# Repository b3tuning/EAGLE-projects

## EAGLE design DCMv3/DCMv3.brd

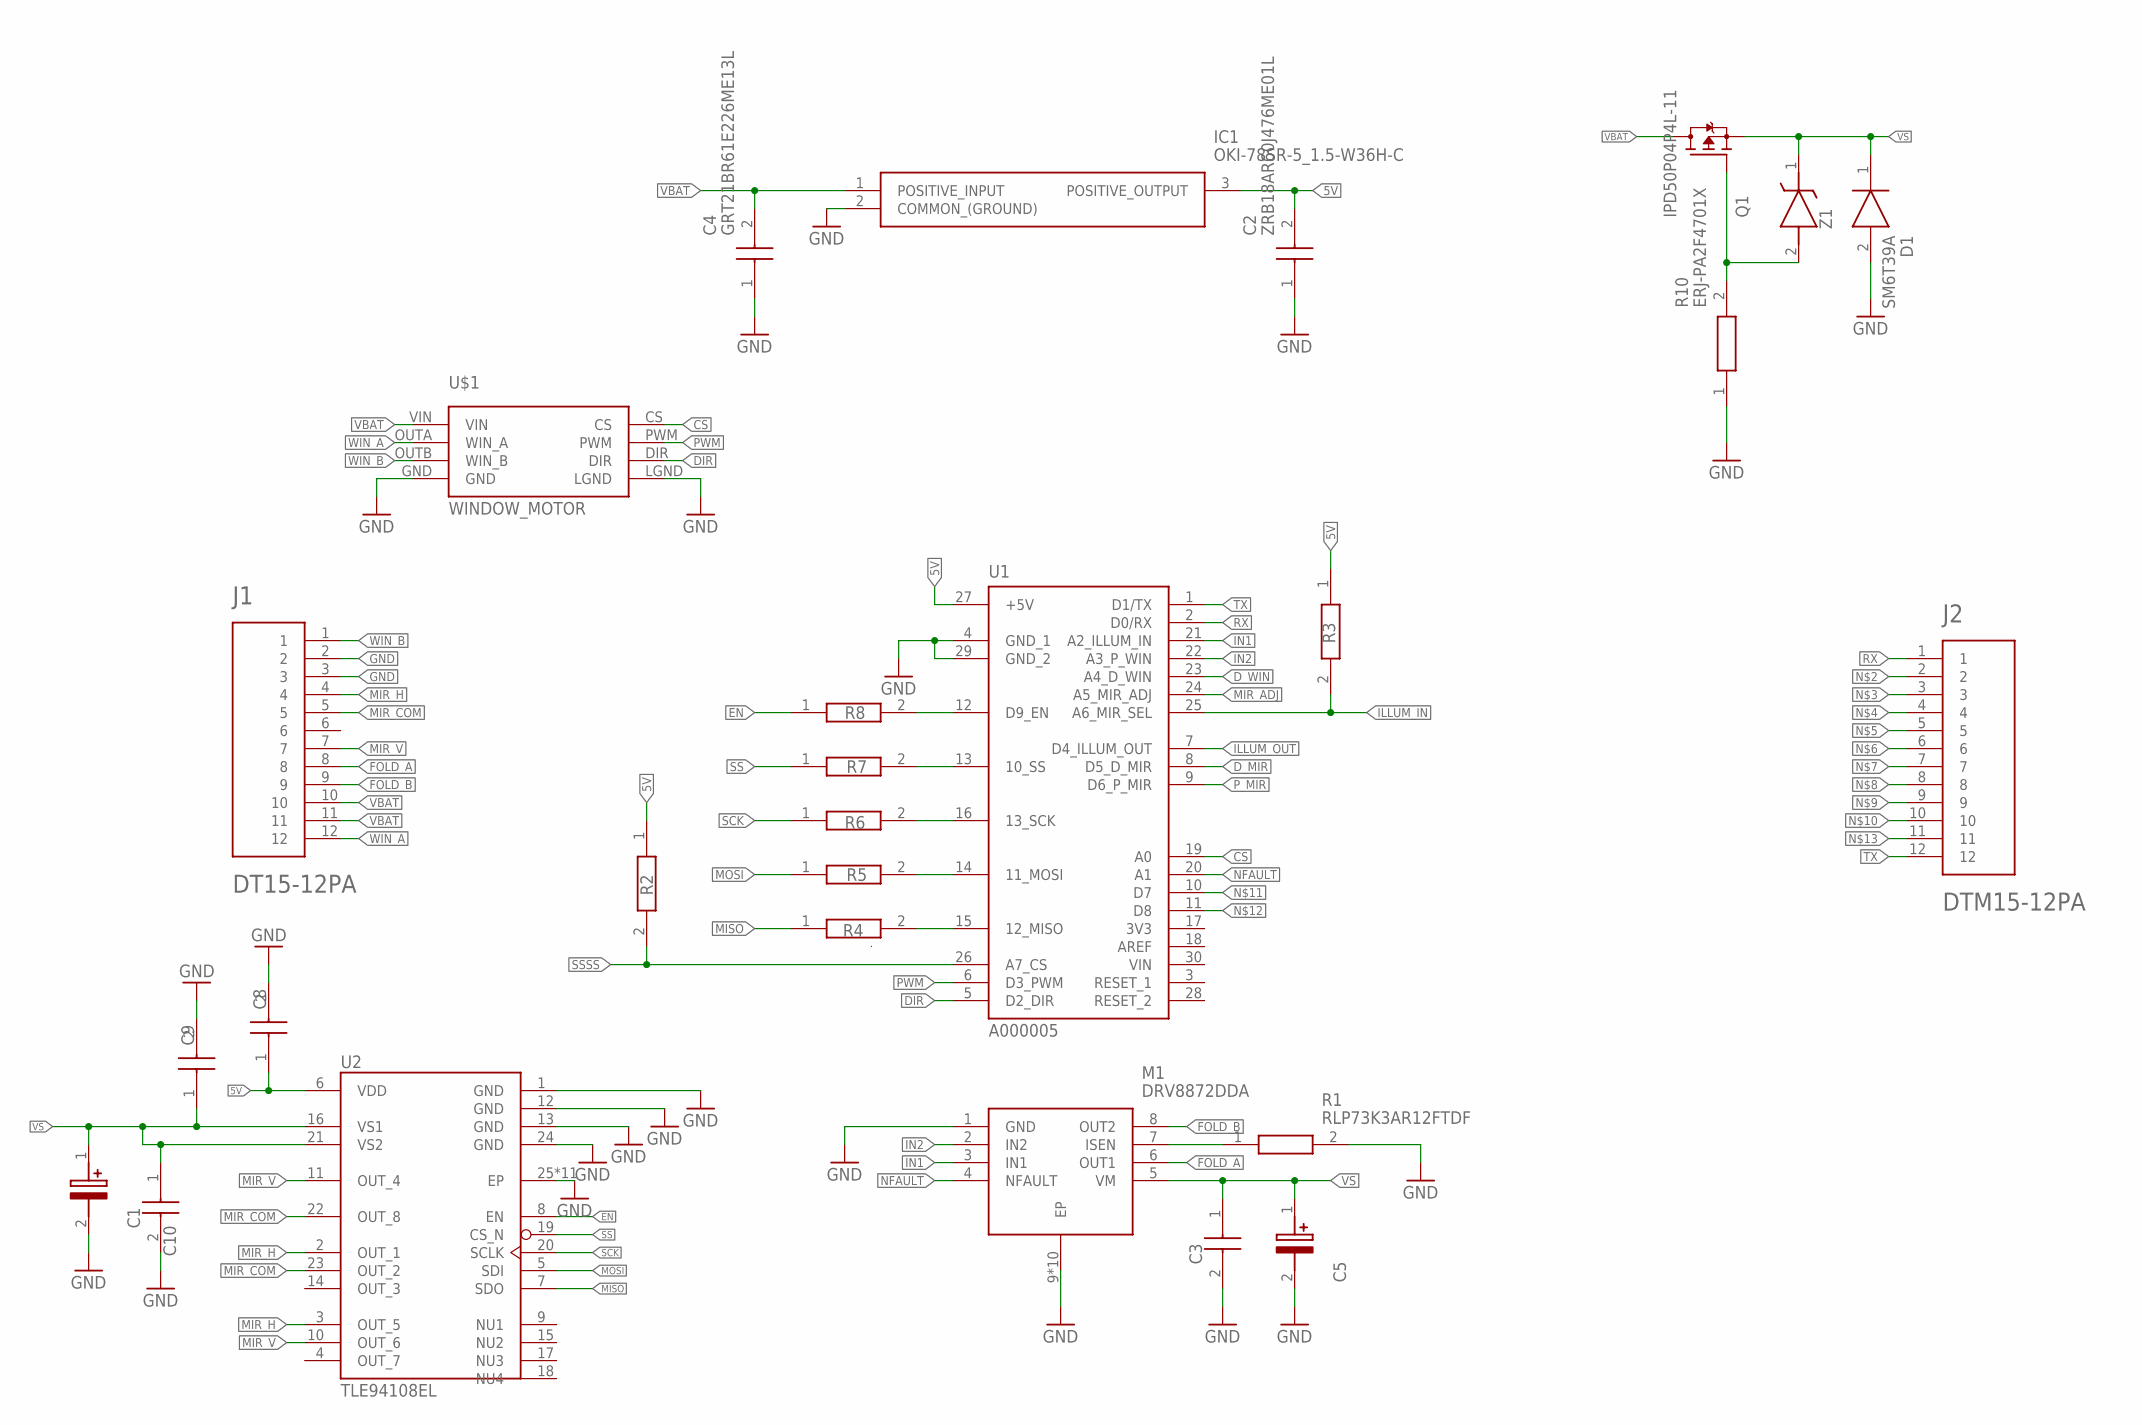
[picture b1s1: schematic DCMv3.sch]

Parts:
C1, C5: EEE-FT1H470AP; CAPAE660X610N
C2: ZRB18AR60J476ME01L; CAPC1608X120N
C3: GRM033R6YA104KE14D; CAPC0603X33N
C4: GRT21BR61E226ME13L; CAPC2012X145N
C8, C9, C10: GRM155R61H104JE14D; CAPC1005X55N
D1: SM6T39A; DIOM5436X265N
IC1: OKI-78SR-5_1.5-W36H-C; OKI-78SR-HORIZONTAL
J1: DT15-12PA; TE_DT15-12PA
J2: DTM15-12PA; TE_DTM15-12PA
M1: DRV8872DDA; SOIC127P600X170-9N
Q1: IPD50P04P4L-11; DPAK228P998X235-3N
R1: RLP73K3AR12FTDF; RESC6432X84N
R2, R3: ERJ-1RHD2202C; RESC0603X26N
R4, R5, R6, R7, R8: ERJ-1RKD4700C; RESC0603X26N
R10: ERJ-PA2F4701X; RESC1005X40N
U1: A000005; ARDUINO_A000005
U2: TLE94108EL; SOP65P600X170-25N
U$1: WINDOW_MOTOR; POLOLU
Z1: MM3Z12VT1G; SOD2512X110N

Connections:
5V: C2.2, C8.1, IC1.3 (POSITIVE_OUTPUT), R2.1, R3.1, U1.27 (+5V), U2.6 (VDD)
A_EN: R8.2, U1.12 (D9_EN)
A_MISO: R4.2, U1.15 (12_MISO)
A_MOSI: R5.2, U1.14 (11_MOSI)
A_SCK: R6.2, U1.16 (13_SCK)
A_SS: R7.2, U1.13 (10_SS)
CS: U1.19 (A0), U$1.CS
DIR: U1.5 (D2_DIR), U$1.DIR
D_MIR: U1.8 (D5_D_MIR)
D_WIN: U1.23 (A4_D_WIN)
EN: R8.1, U2.8 (EN)
FOLD_A: J1.8, M1.6 (OUT1)
FOLD_B: J1.9, M1.8 (OUT2)
GATE: Q1.1 (G), R10.2, Z1.2 (A)
GND: C1.2 (-), C2.1, C3.2, C4.1, C5.2 (-), C8.2, C9.2, C10.2, D1.2 (A), IC1.2 (COMMON_(GROUND)), J1.2, J1.3, M1.1 (GND), M1.9 (EP), M1.P$1 (EP), M1.P$2 (EP), M1.P$3 (EP), M1.P$4 (EP), M1.P$5 (EP), M1.P$6 (EP), M1.P$7 (EP), M1.P$8 (EP), M1.P$9 (EP), R1.2, R10.1, U1.4 (GND_1), U1.29 (GND_2), U2.1 (GND), U2.12 (GND), U2.13 (GND), U2.24 (GND), U2.25 (EP), U2.GND (EP), U2.GND1 (EP), U2.GND2 (EP), U2.GND3 (EP), U2.GND4 (EP), U2.GND5 (EP), U2.GND6 (EP), U2.GND7 (EP), U2.GND8 (EP), U2.GND9 (EP), U$1.GND, U$1.LGND
ILLUM_IN: R3.2, U1.25 (A6_MIR_SEL)
ILLUM_OUT: U1.7 (D4_ILLUM_OUT)
IN1: M1.3 (IN1), U1.21 (A2_ILLUM_IN)
IN2: M1.2 (IN2), U1.22 (A3_P_WIN)
ISEN: M1.7 (ISEN), R1.1
MIR_ADJ: U1.24 (A5_MIR_ADJ)
MIR_COM: J1.5, U2.22 (OUT_8), U2.23 (OUT_2)
MIR_H: J1.4, U2.2 (OUT_1), U2.3 (OUT_5)
MIR_V: J1.7, U2.10 (OUT_6), U2.11 (OUT_4)
MISO: R4.1, U2.7 (SDO)
MOSI: R5.1, U2.5 (SDI)
NFAULT: M1.4 (NFAULT), U1.20 (A1)
PWM: U1.6 (D3_PWM), U$1.PWM
P_MIR: U1.9 (D6_P_MIR)
RX: J2.1, U1.2 (D0/RX)
SCK: R6.1, U2.20 (SCLK)
SS: R7.1, U2.19 (CS_N)
SSSS: R2.2, U1.26 (A7_CS)
TX: J2.12, U1.1 (D1/TX)
VBAT: C4.2, IC1.1 (POSITIVE_INPUT), J1.10, J1.11, Q1.2 (D), U$1.VIN
VS: C1.1 (+), C3.1, C5.1 (+), C9.1, C10.1, D1.1 (K), M1.5 (VM), Q1.3 (S), U2.16 (VS1), U2.21 (VS2), Z1.1 (K)
WIN_A: J1.12, U$1.OUTA (WIN_A)
WIN_B: J1.1, U$1.OUTB (WIN_B)

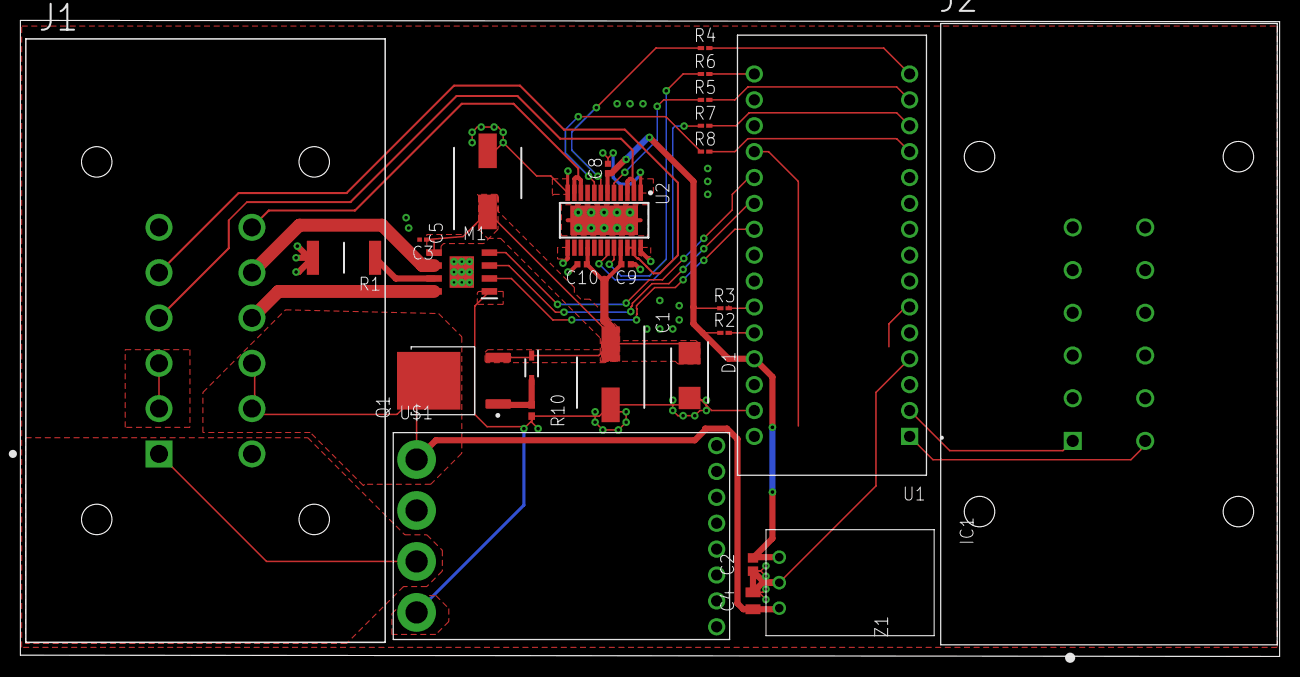
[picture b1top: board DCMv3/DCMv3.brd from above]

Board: 2 copper layers, 123.6 x 62.4 mm, 27 parts (0 on the bottom side), 33 nets.

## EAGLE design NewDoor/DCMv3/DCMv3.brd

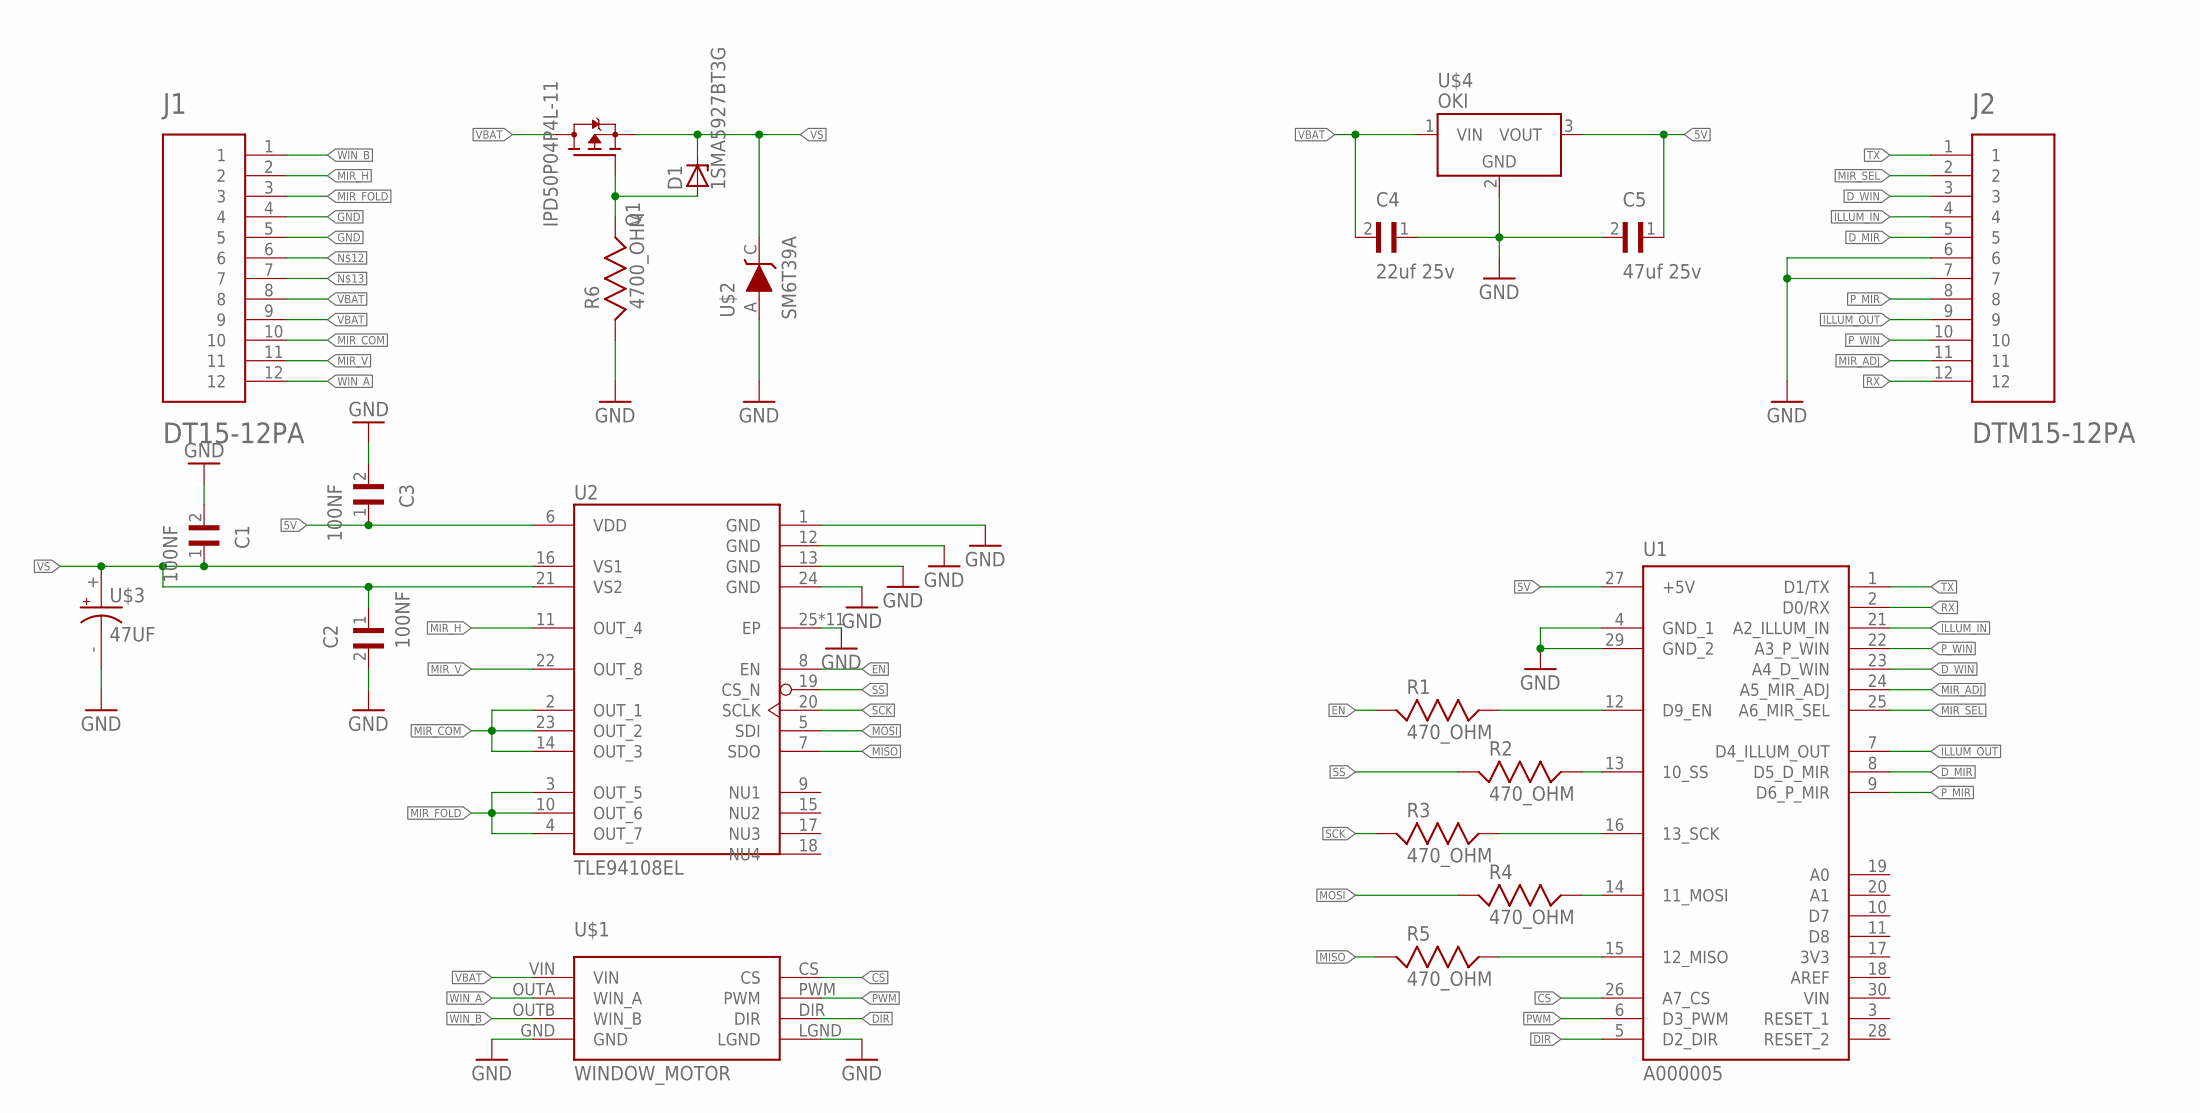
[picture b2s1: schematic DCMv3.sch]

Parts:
C1, C2, C3: 100NF; CAPC3216X110N
C4: 22uf 25v; CAP3216X125N
C5: 47uf 25v; CAP3216X125N
D1: 1SMA5927BT3G; DO214AC
J1: DT15-12PA; TE_DT15-12PA
J2: DTM15-12PA; TE_DTM15-12PA
Q1: IPD50P04P4L-11; DPAK228P998X235-3N
R1, R2, R3, R4, R5: 470_OHM; RESC3216X65
R6: 4700_OHM; RESC3216X70
U1: A000005; ARDUINO_A000005
U2: TLE94108EL; SOP65P600X170-25N
U$1: WINDOW_MOTOR; POLOLU
U$2: SM6T39A
U$3: 47UF; CAPAE1030X1200
U$4: OKI; OKI-78SR-H

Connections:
5V: C3.1, C5.1, U1.27 (+5V), U2.6 (VDD), U$4.3 (VOUT)
CS: U1.26 (A7_CS), U$1.CS
DIR: U1.5 (D2_DIR), U$1.DIR
D_MIR: J2.5, U1.8 (D5_D_MIR)
D_WIN: J2.3, U1.23 (A4_D_WIN)
EN: R1.1, U2.8 (EN)
EN_A: R1.2, U1.12 (D9_EN)
GATE: D1.A, Q1.1 (G), R6.2
GND: C1.2, C2.2, C3.2, C4.1, C5.2, J1.4, J1.5, J2.6, J2.7, R6.1, U1.4 (GND_1), U1.29 (GND_2), U2.1 (GND), U2.12 (GND), U2.13 (GND), U2.24 (GND), U2.25 (EP), U2.GND (EP), U2.GND1 (EP), U2.GND2 (EP), U2.GND3 (EP), U2.GND4 (EP), U2.GND5 (EP), U2.GND6 (EP), U2.GND7 (EP), U2.GND8 (EP), U2.GND9 (EP), U$1.GND, U$1.LGND, U$2.A, U$3.-, U$4.2 (GND)
ILLUM_IN: J2.4, U1.21 (A2_ILLUM_IN)
ILLUM_OUT: J2.9, U1.7 (D4_ILLUM_OUT)
MIR_ADJ: J2.11, U1.24 (A5_MIR_ADJ)
MIR_COM: J1.10, U2.2 (OUT_1), U2.14 (OUT_3), U2.23 (OUT_2)
MIR_FOLD: J1.3, U2.3 (OUT_5), U2.4 (OUT_7), U2.10 (OUT_6)
MIR_H: J1.2, U2.11 (OUT_4)
MIR_SEL: J2.2, U1.25 (A6_MIR_SEL)
MIR_V: J1.11, U2.22 (OUT_8)
MISO: R5.1, U2.7 (SDO)
MISO_A: R5.2, U1.15 (12_MISO)
MOSI: R4.1, U2.5 (SDI)
MOSI_A: R4.2, U1.14 (11_MOSI)
PWM: U1.6 (D3_PWM), U$1.PWM
P_MIR: J2.8, U1.9 (D6_P_MIR)
P_WIN: J2.10, U1.22 (A3_P_WIN)
RX: J2.12, U1.2 (D0/RX)
SCK: R3.1, U2.20 (SCLK)
SCK_A: R3.2, U1.16 (13_SCK)
SS: R2.1, U2.19 (CS_N)
SS_A: R2.2, U1.13 (10_SS)
TX: J2.1, U1.1 (D1/TX)
VBAT: C4.2, J1.8, J1.9, Q1.2 (D), U$1.VIN, U$4.1 (VIN)
VS: C1.1, C2.1, D1.C, Q1.3 (S), U2.16 (VS1), U2.21 (VS2), U$2.C, U$3.+
WIN_A: J1.12, U$1.OUTA (WIN_A)
WIN_B: J1.1, U$1.OUTB (WIN_B)

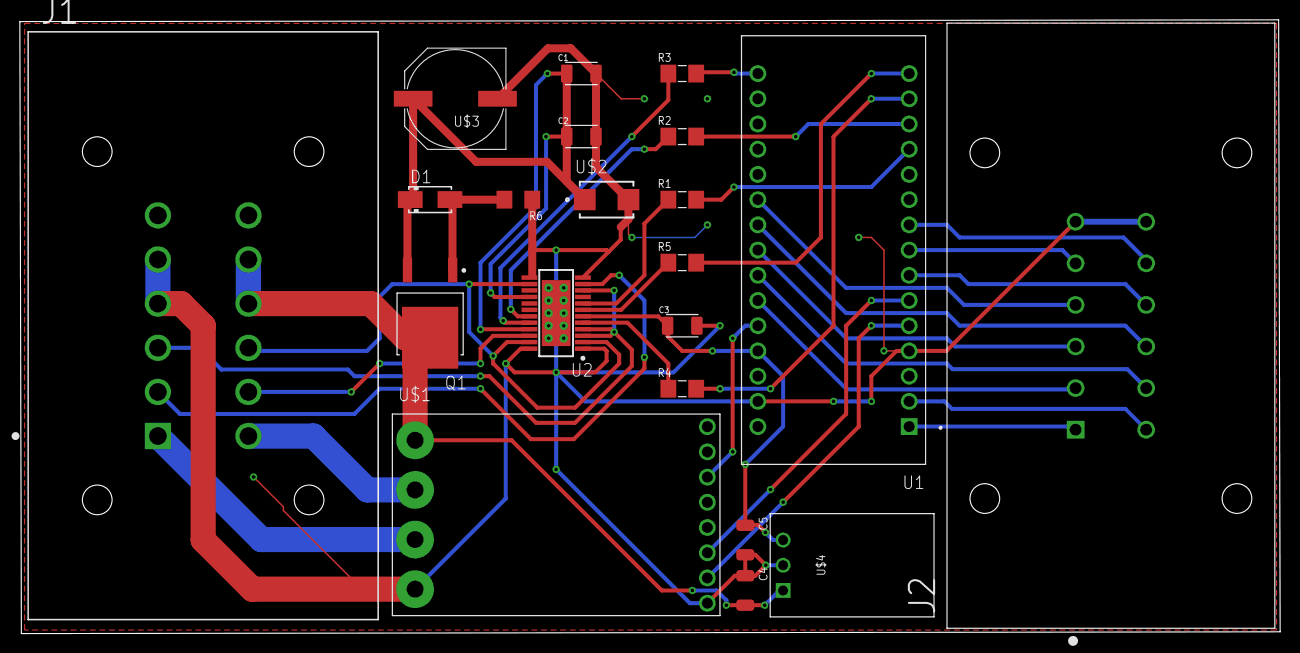
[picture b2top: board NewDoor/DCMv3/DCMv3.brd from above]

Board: 2 copper layers, 127.0 x 61.8 mm, 21 parts (0 on the bottom side), 34 nets.

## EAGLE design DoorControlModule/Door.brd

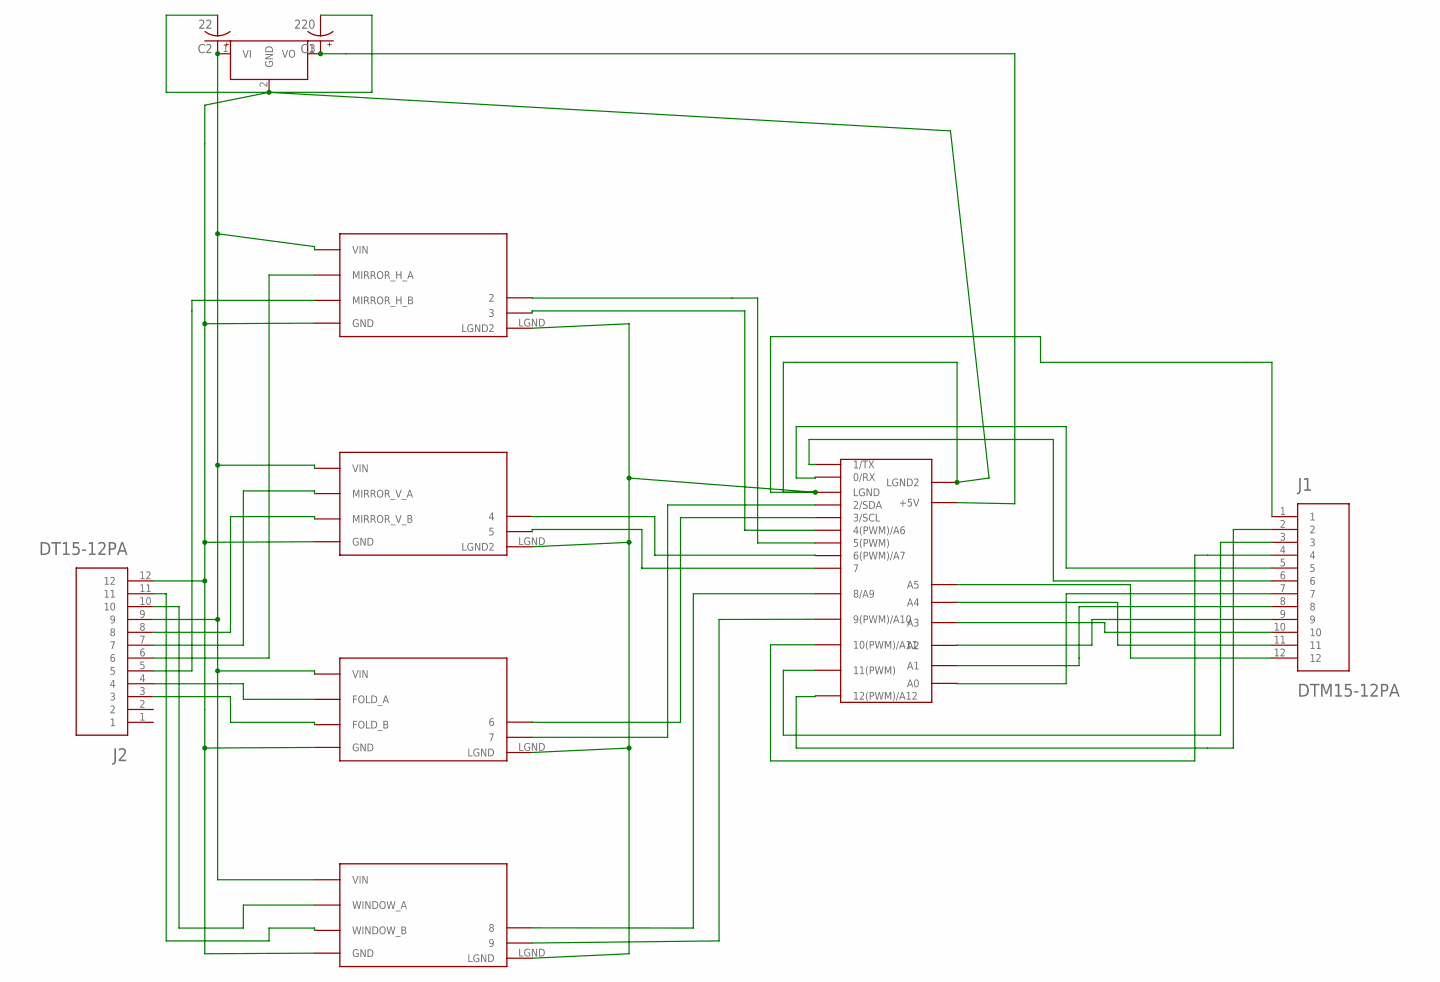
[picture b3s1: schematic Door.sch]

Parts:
C1: 220; 8MMCAP
C2: 22; 8MMCAP
FOLD: FOLD_MOTOR; POLOLU
HMIRROR: MIRROR_H_MOTOR; POLOLU
J1: DTM15-12PA; TE_DTM15-12PA
J2: DT15-12PA; TE_DT15-12PA
U$5: ARDUINO_MICRO_NEW
U$6: DCDC_OKI-78SR; OKI-78SRH
VMIRROR: MIRROR_V_MOTOR; POLOLU
WNDOW: WINDOW_MOTOR; POLOLU

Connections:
5V: C1.+, U$5.+5V, U$6.3 (VO)
GND: C1.-, C2.-, FOLD.GND, FOLD.LGND, HMIRROR.GND, HMIRROR.LGND (LGND2), J1.1, J2.12, U$5.LGND, U$5.LGND2, U$6.2 (GND), VMIRROR.GND, VMIRROR.LGND (LGND2), WNDOW.GND, WNDOW.LGND
unnamed: FOLD.DIR (7), U$5.2/SDA
unnamed: FOLD.PWM (6), U$5.3/SCL
unnamed: HMIRROR.PWM (2), U$5.5(PWM)
unnamed: HMIRROR.DIR (3), U$5.4(PWM)/A6
unnamed: J1.12, U$5.A5
unnamed: J1.11, U$5.A4
unnamed: U$5.8/A9, WNDOW.PWM (8)
unnamed: U$5.9(PWM)/A10, WNDOW.DIR (9)
unnamed: J1.10, U$5.A3
unnamed: J1.6, U$5.1/TX
unnamed: FOLD.OUTA (FOLD_A), J2.4
unnamed: J2.8, VMIRROR.OUTB (MIRROR_V_B)
unnamed: J2.7, VMIRROR.OUTA (MIRROR_V_A)
unnamed: J2.11, WNDOW.OUTB (WINDOW_B)
unnamed: J2.10, WNDOW.OUTA (WINDOW_A)
unnamed: FOLD.OUTB (FOLD_B), J2.3
unnamed: HMIRROR.OUTB (MIRROR_H_B), J2.5
unnamed: HMIRROR.OUTA (MIRROR_H_A), J2.6
unnamed: J1.9, U$5.A2
unnamed: J1.8, U$5.A1
unnamed: J1.7, U$5.A0
unnamed: U$5.6(PWM)/A7, VMIRROR.PWM (4)
unnamed: U$5.7, VMIRROR.DIR (5)
unnamed: J1.5, U$5.0/RX
unnamed: J1.2, U$5.12(PWM)/A12
unnamed: J1.3, U$5.11(PWM)
unnamed: J1.4, U$5.10(PWM)/A11
VIN: C2.+, FOLD.VIN, HMIRROR.VIN, J2.9, U$6.1 (VI), VMIRROR.VIN, WNDOW.VIN

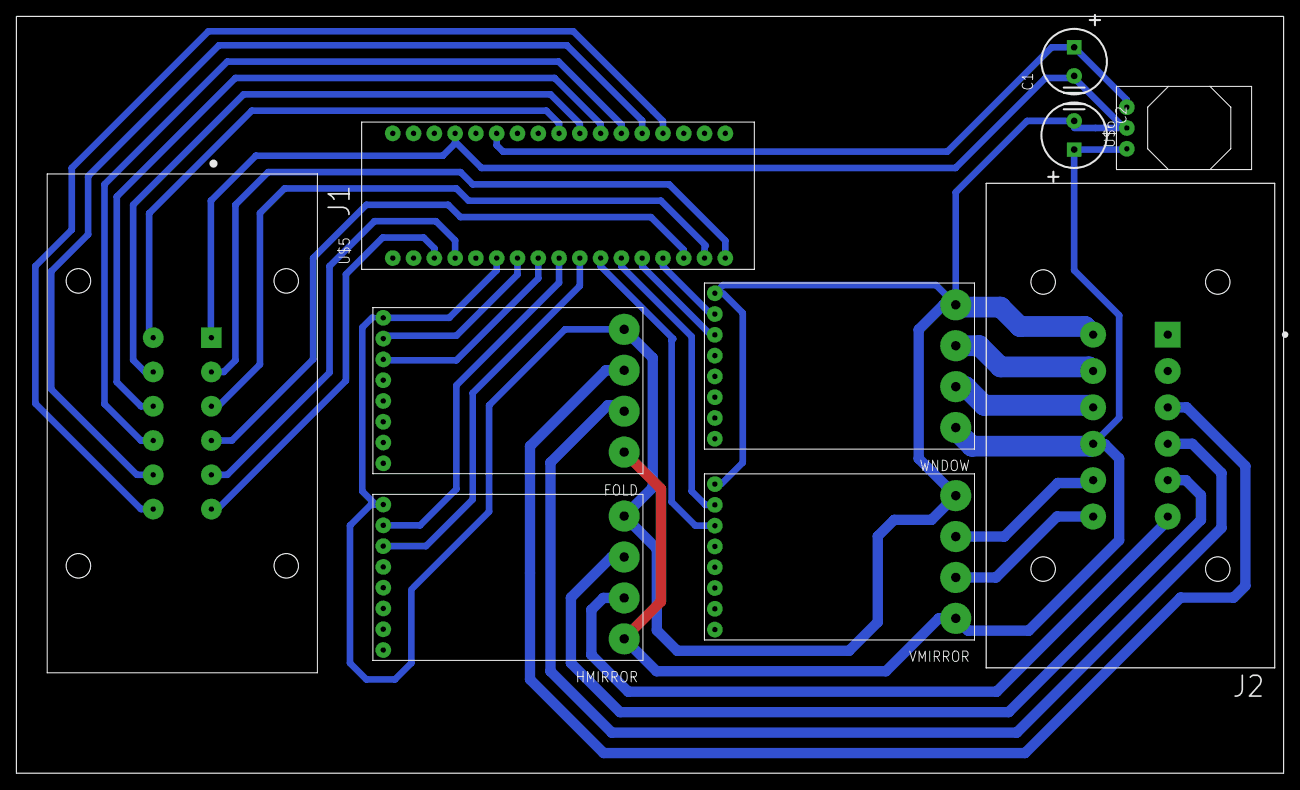
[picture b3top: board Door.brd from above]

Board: 2 copper layers, 154.9 x 92.5 mm, 10 parts (0 on the bottom side), 30 nets.

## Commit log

2019-07-10 adding DCM projects
2019-07-10 adding more DCM projects
2019-07-11 updating DCMv3
    x
2019-07-11 added current sense resistor
